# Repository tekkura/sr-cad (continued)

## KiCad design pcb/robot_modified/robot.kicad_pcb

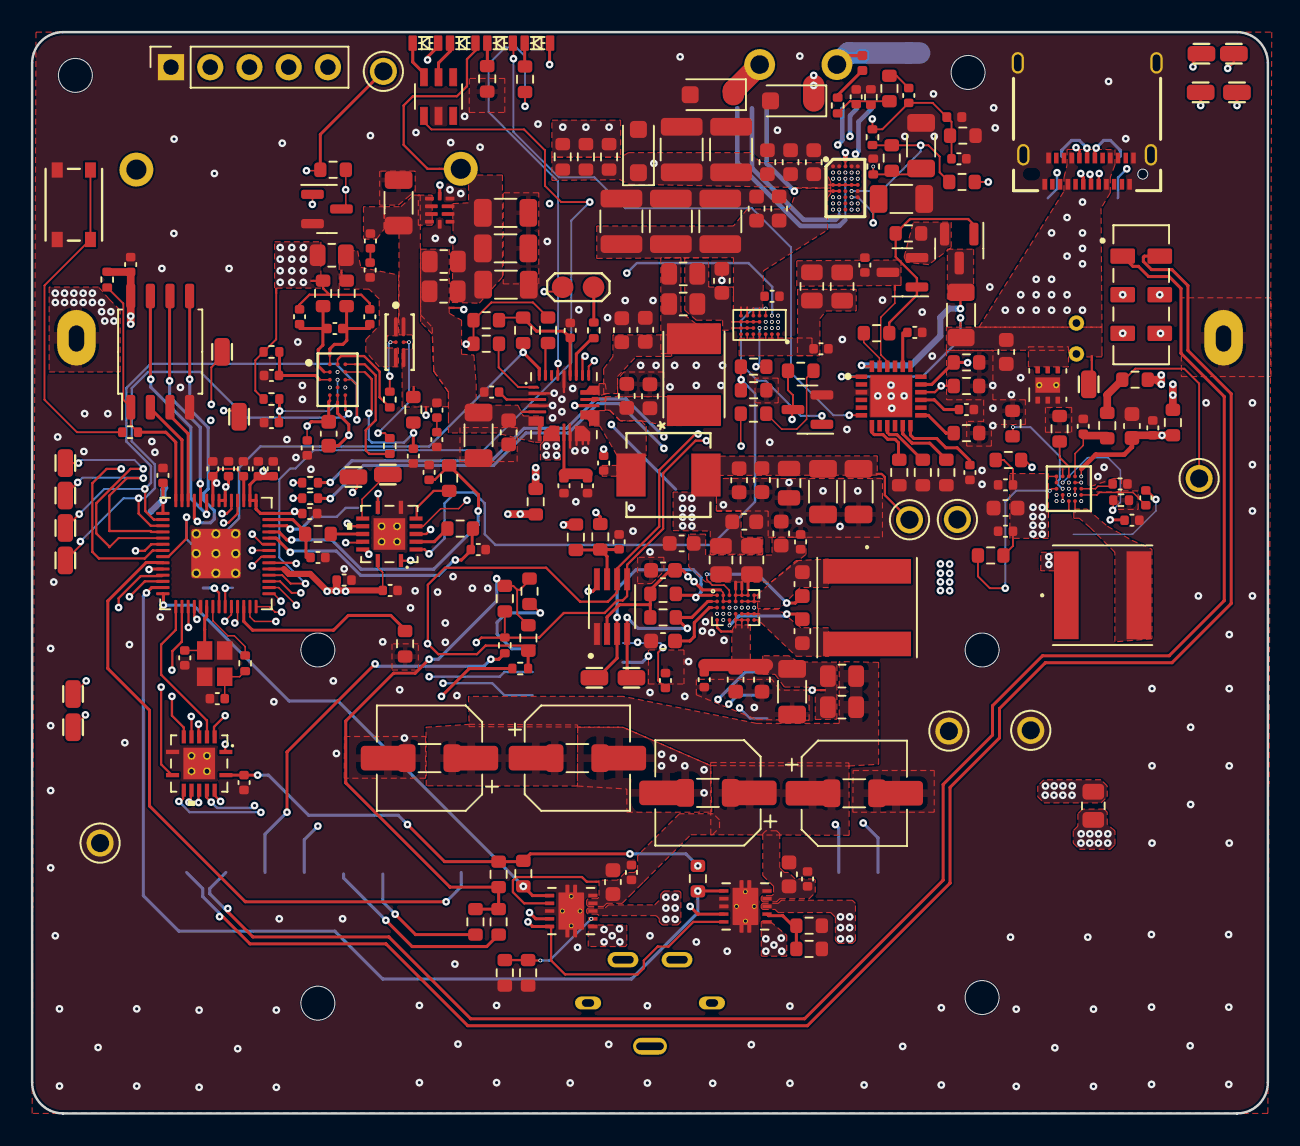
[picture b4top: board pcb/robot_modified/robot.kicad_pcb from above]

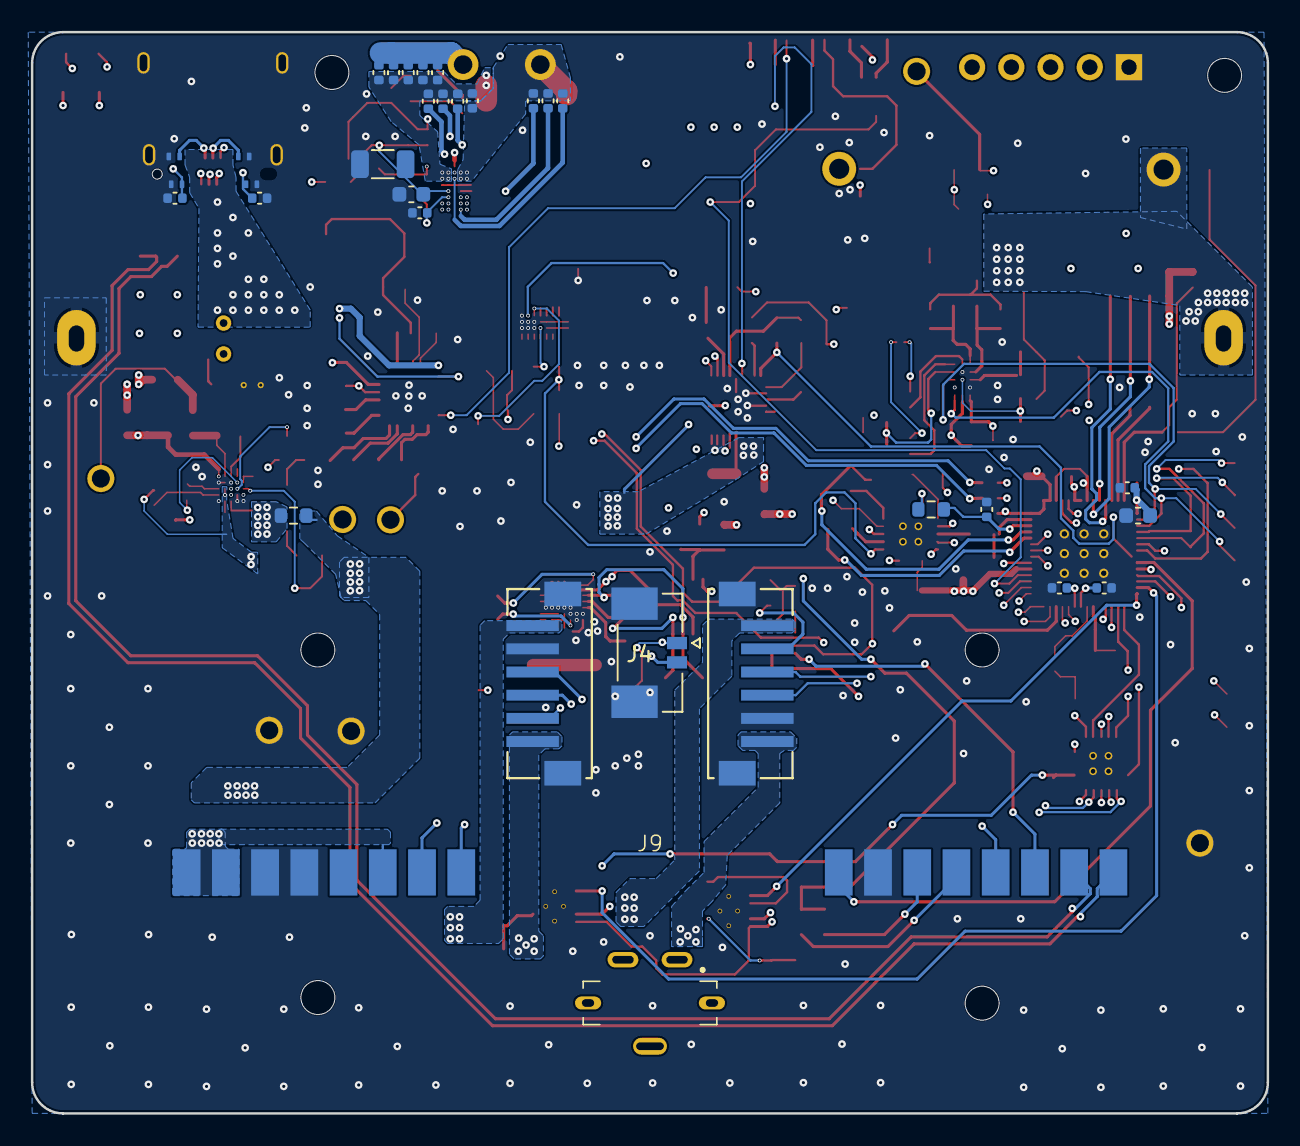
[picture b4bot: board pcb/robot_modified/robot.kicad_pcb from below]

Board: 4 copper layers, 80.0 x 70.0 mm, 318 parts (39 on the bottom side), 202 nets.

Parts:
BT1: DNP; battery26650_holderOnly
BT2: DNP; battery26650
C1, C33, C34, C76, C78, C87, C93: 22uF; C_0603_1608Metric
C2, C3, C18, C19: 27pF; C_0402_1005Metric
C4, C8, C10, C21, C22, C29, C55, C69, C88, C94, C95, C99, C105, C126: 1uF; C_0402_1005Metric
C5, C6, C7, C9, C11, C12, C13, C14, C15, C16, C24, C32, C35, C36, C37, C38, C39, C40, C41, C44, C57, C58, C59, C60, C61, C62, C63, C64, C65, C66, C70, C71, C72, C73, C85, C92, C102, C103, C104, C113, C114, C116, C119, C121: 0.1uF; C_0402_1005Metric
C17, C20, C25, C27, C42, C43, C67, C68, C75, C77, C80, C129, C130, C132, C134, C136: 10uF; C_0603_1608Metric
C23, C124: 4.7uF; C_0603_1608Metric
C26, C56: 0.47uF; C_0603_1608Metric
C28: 2.2uF; C_0603_1608Metric
C30, C31: 0.22uF; C_0603_1608Metric
C74, C86, C89, C90: 100uF; CP_Elec_APXJ100ARA271MF61G
C79, C82, C83, C91, C96, C106, C107, C108, C109, C125, C127: 100uF; C_1206_3216Metric
C81: 47uF; C_0805_2012Metric
C84, C115, C118: 10nF; C_0402_1005Metric
C110, C117, C120: 22nF; C_0402_1005Metric
C111: 1.5nF; C_0402_1005Metric
C112, C122: 3.3nF; C_0402_1005Metric
C123, C128: 47nF; C_0402_1005Metric
C131, C133, C135, C137, C138: 100uF; C_1210_3225Metric
D1: LED-RED; B12H1UYG-20D000134U1930
D2: LED-YG; B12H1UYG-20D000134U1930
D3: LED-Amber; B12H1UYG-20D000134U1930
D4, D6, D10: SMF13A; D_SOD-123F
D5: LED-GREEN; B12H1UYG-20D000134U1930
D7: D_Schottky; SD2114S040S8R0
D9, D11: IN4448HLP; D_0402_1005Metric
H1, H2, H5, H6: MountingHole; MountingHole_2.2mm_M2_2mm_clearance
H3, H4: MountingHole; MountingHole_2.2mm_M2
IC1: TPS22998RYZR
J1: USBC_Receptacle_SMD_RA; CON_USB3.1-C_RCPT_SMD_RA_ACP_12401610E4#2A
J2: Conn_01x05; PinSocket_1x05_P2.54mm_Vertical
J3, J5: Conn_01x06_MountingPin; CONN_B6B-ZR-SM4-TF_JST
J4: USB4151-GF-C; GCT_USB4151-GF-C_REVA
J8: Conn_01x02; THT_Pitch5mm_Drill1.2mm
J9: Conn_01x16; SMD FOR CASTELLATED 1x16 2.54mm
L1, L3: 1.5uH; NRS6028T1R5NMGJ
L2: 0.47uH; Vishay-IHLP-2020BZ-FP_1.905x2.79-3D_2.0-0-0-MFG
NT1, NT2, NT3, NT4, NT5, NT6, NT7, NT8, NT9, NT10, NT11, NT12, NT13, NT14, NT15, NT16, NT17, NT18, NT20: NetTie_2; NetTie-_SMD_Pad6mil
Q1, Q7: Q_NMOS_GDS; SOT-23
Q2: EFC8811R-TF; ON_Semiconductor-568AL-10_2013-O-MFG
Q3: AS2312; SOT-23
Q4: YJL3416A; SOT-23
Q5, Q6: SN74AHC125RGYR
R1, R5, R46, R47, R50: 1k; R_0402_1005Metric
R2: DNP; R_0402_1005Metric
R3, R4: 27; R_0402_1005Metric
R6, R7, R41, R42: 10; R_0402_1005Metric
R8, R18: 47K; R_0603_1608Metric
R9: 80.6k; R_0402_1005Metric
R10, R76, R79, R80, R81, R82, R83, R84, R85, R86, R87, R88, R90, R91, R92, R93, R94: 0; R_0603_1608Metric
R11, R52, R54, R67, R68, R69, R70, R71, R72, R77, R78: 0; R_0805_2012Metric
R14, R15, R20, R21: 2.2k; R_0603_1608Metric
R16: 510k; R_0603_1608Metric
R17, R49, R59, R60, R61, R89, R99: 100k; R_0603_1608Metric
R19: 200k; R_0603_1608Metric
R22, R23, R24, R25, R56, R58, R97: 100; R_0603_1608Metric
R26, R27, R29, R30: 0.39; R_0603_1608Metric
R28, R31, R96, R102: 10k; R_0603_1608Metric
R43, R45, R103, R104, R105: 200; R_0603_1608Metric
R44: 5m; R_0805_2012Metric
R48: 2k; R_0603_1608Metric
R51: 10m; R_1206_3216Metric
R53: 113K; R_0603_1608Metric
R55: 14k; R_0603_1608Metric
R62: 16k; R_0603_1608Metric
R63, R64: 5.1k; R_0603_1608Metric
R66: DNP; R_0603_1608Metric
R98: 150k; R_0402_1005Metric
R100: 220k; R_0402_1005Metric
R101: 6.8k; R_0402_1005Metric
S2: PTS815 SJM 250 SMTR LFS; SW4_PTS815 SJM 250 SMTR LFS_CNK
S3: JS202011JCQN; SW_JS202011JCQN
SW1: SW_SPST; MOLEX_picoblade_SMT_2pin
TH1: DNP; battery26650_thermistor
TH2: 100k; R_0402_1005Metric
TP1, TP2, TP9, TP10, TP11, TP16, TP17, TP18, TP19, TP20, TP21, TP22, TP23, TP24, TP26, TP27, TP33: SMD_0603; TestPoint_SMD_0603
TP12: TP2PinPads; TestPoint_2Pads_Pitch2mm_SMD
TP28, TP29: TestPoint; THT_JumperLead
TP30, TP34, TP39, TP40, TP41, TP42, TP43: TestPoint; KEYSTONE_5002
U1: STWLC38JRM; BGA40C40P5X8_213X333X57
U2: W25Q128JVS; SOIC-8_5.23x5.23mm_P1.27mm
U3: RP2040; RP2040-QFN-56
U4: NCP3901
U5: LSF0102DCTR; SOP65P400X130-8N
U6: MAX77857BEWB+; WLP-35_7x5_2.828x2.028mm
U7: AP2502KTR-G1; SOT95P280X145-6N
U8, U9: DRV8830DRCR; IC_DRV8830DRCR
U12: BQ27742YZFR-G1; Texas_Instruments-YZF0015-0-0-MFG
U13: MAX77976EFD+; MAX77976
U14: MAX77642ANA+; Maxim-N252B2-1-0-A-MFG
U18: AP33771DKZ-13; AP33771DKZ13
U25: TVS0500DRV; TVS0500DRVR
U26, U27, U28, U29: TPD1E05U06; TPD1E05U06DPYR
Y1: ECS-120-8-36-CKM-TR3; XTAL_ECS-120-8-36-CKM-TR3

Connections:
/1V8: R83.2, R91.2, TP40.1
/3V3: R8.1, R14.1, R15.1, R76.2, R79.2, R80.2, R81.2, R82.2, R84.2, R85.2, R86.1, R87.1, R88.2, R94.2, TP39.1
/ADC0: Q5.2 (1A), R16.2, R17.1
/BoostRegulator/1V8: C26.1, R20.1, R21.1, R83.1, U5.2 (VREF_A), U6.A2 (VIO), U6.B2 (EN), U6.B3 (EN)
/BoostRegulator/3V3: C24.1, R19.1, R82.1, U5.7 (VREF_B)
/BoostRegulator/IN: C25.1, C27.1, C29.2, R69.2, R70.2, U6.A4 (IN), U6.A5 (IN), U6.A6 (IN), U6.B4 (IN)
/Charger/BATT: C75.1, C79.1, NT5.1, NT6.1, R77.2, R78.2, U13.6 (BATT), U13.7 (BATT), U13.8 (BATT)
/Charger/BATT_SIGNAL: NT5.2, U13.5 (BATSP)
/Charger/DISQBAT: R80.1, U13.1 (DISQBAT)
/Charger/PVDD: C69.1, C70.1, U13.12 (PVDD)
/Charger/SUSPND: R81.1, U13.31 (SUSPND)
/Charger/VIO: C71.1, R49.1, R79.1, U13.27 (VIO)
/Charger/V_IN: C67.1, C68.1, D7.2 (Anode), R67.2, R68.2, U13.22 (CHGIN), U13.23 (CHGIN)
/DN1: J9.16, S3.4
/DN2: J1.A7 (D-), J1.B7 (D-), S3.6, U28.1 (I/O)
/DP1: J9.15, S3.1
/DP2: J1.A6 (D+), J1.B6 (D+), S3.3, U29.1 (I/O)
/GPIO4: Q1.3 (D), R18.2, U3.6 (GPIO4)
/GPIO5: U3.7 (GPIO5), U4.D2 (VINA_EN/OTG_EN)
/GPIO6: R49.2, U3.8 (GPIO6), U13.32 (IRQB)
/GPIO7: J9.9, U3.9 (GPIO7)
/GPIO8: Q6.1 (1~OE), Q6.4 (2~OE), Q6.10 (3~OE), Q6.13 (4~OE), U3.11 (GPIO8)
/GPIO9: U1.G4 (ENB), U3.12 (GPIO9)
/GPIO10: R28.2, U3.13 (GPIO10), U8.6 (~FAULT)
/GPIO11: R31.2, U3.14 (GPIO11), U9.6 (~FAULT)
/GPIO12: Q6.3 (1Y), U3.15 (GPIO12)
/GPIO13: Q6.6 (2Y), U3.16 (GPIO13)
/GPIO14: Q6.8 (3Y), U3.17 (GPIO14)
/GPIO15: Q6.11 (4Y), U3.18 (GPIO15)
/GPIO20: Q7.3 (D), R8.2, U3.31 (GPIO20)
/GPIO23: R89.2, U1.H4 (INTB), U3.35 (GPIO23)
/I2C0_SCL: R7.2, R15.2, TP16.1, U1.H5 (SCL), U3.3 (GPIO1), U5.6 (B1), U8.10 (SCL), U9.10 (SCL), U12.E3 (SCL)
/I2C0_SDA: R6.2, R14.2, TP1.1, U1.G5 (SDA), U3.2 (GPIO0), U5.5 (B2), U8.9 (SDA), U9.9 (SDA), U12.C3 (SDA)
/I2C1_SCL: J9.7, TP2.1, U3.5 (GPIO3), U13.24 (SCL)
/I2C1_SDA: J9.8, TP17.1, U3.4 (GPIO2), U13.25 (SDA)
/LDOs/LED_3V3: D2.1 (K), U7.6 (LED1)
/LDOs/SYS: C4.1, C85.1, C87.1, R90.2, R92.2, R93.2, U14.A1 (SYSA), U14.B1 (SYSA), U14.E3 (IN_SBB)
/LED_EN: U3.32 (GPIO21), U7.1 (EN)
/LED_PACK: D3.1 (K), U7.5 (LED2)
/MCU/3V3: C5.1, C9.1, C10.1, C11.1, C12.1, C13.1, C14.1, C15.1, C16.1, C17.1, C35.1, Q5.14 (VCC), R2.1, R86.2, U2.8 (VCC), U3.1 (IOVDD), U3.10 (IOVDD), U3.22 (IOVDD), U3.33 (IOVDD), U3.42 (IOVDD), U3.43 (ADC_AVDD), U3.44 (VREG_IN), U3.48 (USB_VDD), U3.49 (IOVDD)
/MCU/ADC2: Q5.9 (3A), TP26.1
/MCU/ADC3: Q5.12 (4A), TP27.1
/MCU/D+: R3.1, S3.2, TP20.1
/MCU/D-: R4.1, S3.5, TP21.1
/MCU/GPIO22: Q5.1 (1~OE), Q5.4 (2~OE), Q5.10 (3~OE), Q5.13 (4~OE), U3.34 (GPIO22)
/MCU/GPIO24: TP10.1, U3.36 (GPIO24)
/MCU/GPIO25: TP33.1, U3.37 (GPIO25)
/MCU/GPIO26_ADC0: C39.1, R25.1, U3.38 (GPIO26_ADC0)
/MCU/GPIO27_ADC1: C38.1, R24.1, U3.39 (GPIO27_ADC1)
/MCU/GPIO28_ADC2: C37.1, R23.1, U3.40 (GPIO28_ADC2)
/MCU/GPIO29_ADC3: C36.1, R22.1, U3.41 (GPIO29_ADC3)
/MCU/QSPI_SCLK: U2.6 (CLK), U3.52 (QSPI_SCLK)
/MCU/QSPI_SD0: U2.5 (DI(IO0)), U3.53 (QSPI_SD0)
/MCU/QSPI_SD1: U2.2 (DO(IO1)), U3.55 (QSPI_SD1)
/MCU/QSPI_SD2: U2.3 (IO2), U3.54 (QSPI_SD2)
/MCU/QSPI_SD3: U2.7 (IO3), U3.51 (QSPI_SD3)
/MCU/QSPI_SS: R1.1, R2.2, U2.1 (~CS), U3.56 (QSPI_SS)
/MCU/RUN: R10.2, U3.26 (RUN)
/MCU/SWCLK: J2.2, U3.24 (SWCLK)
/MCU/SWD: J2.3, U3.25 (SWD)
/MCU/UART_CTS: TP11.1, U3.29 (GPIO18)
/MCU/UART_RTS: TP24.1, U3.30 (GPIO19)
/MCU/UART_RX: J2.5, U3.28 (GPIO17)
/MCU/UART_TX: J2.4, U3.27 (GPIO16)
/MCU/XIN: C2.1, U3.20 (XIN), Y1.1
/MCU/XOUT: R5.1, U3.21 (XOUT)
/MCU/~USB_BOOT: R1.2, S2.1, S2.2
/MOTORS/ENC_11: J5.3, Q6.2 (1A)
/MOTORS/ENC_12: J5.4, Q6.5 (2A)
/MOTORS/ENC_21: J3.4, Q6.9 (3A)
/MOTORS/ENC_22: J3.3, Q6.12 (4A)
/MOTORS/ENC_VCC: J3.5, J5.5, R84.1
/MOTORS/OUT_N1: J5.6, U8.1 (OUT2)
/MOTORS/OUT_N2: J3.1, U9.1 (OUT2)
/MOTORS/OUT_P1: J5.1, U8.3 (OUT1)
/MOTORS/OUT_P2: J3.6, U9.3 (OUT1)
/MOTORS/VCC: C40.1, C41.1, C42.1, C43.1, C74.1, C86.1, C89.1, C90.1, NT17.2, R71.1, R72.1, U8.4 (VCC), U9.4 (VCC)
/MOTORS/VIO: C44.1, Q6.14 (VCC), R28.1, R31.1, R85.1
/PowerMux/FLAG: Q1.1 (G), U4.D3 (VINB_EN/FLAG)
/PowerMux/VIN_A: C21.1, R52.2, R54.2, U4.A1 (VINA), U4.A2 (VINA), U4.A3 (VINA), U4.A4 (VINA), U4.A5 (VINA), U4.A6 (VINA), U4.A7 (VINA)
/PowerMux/VIN_B: C22.1, C129.2, C130.2, C131.2, C133.2, C135.2, U1.E1 (VOUT_1), U1.E2 (VOUT_2), U4.D4 (VINB), U4.D5 (VINB), U4.D6 (VINB), U4.D7 (VINB)
/PowerMux/VIO: R18.1, R76.1
/PowerMux/VOUT: C23.1, R67.1, R68.1, U4.B5 (OUT), U4.B6 (OUT), U4.B7 (OUT), U4.C4 (OUT), U4.C5 (OUT), U4.C6 (OUT), U4.C7 (OUT)
/Protection/PACK+: C106.1, C107.1, C108.1, IC1.6 (VOUT_1), IC1.7 (VOUT_2), IC1.8 (VOUT_3), NT7.1, R77.1, R78.1, TP29.1
/Protection/RC2: Q7.1 (G), U12.D3 (RC2)
/SCL_SL: J9.13, R7.1
/SDA_SL: J9.14, R6.1
/SYS: C1.1, C76.1, C78.1, C81.1, C82.1, C83.1, L2.2, NT11.1, NT14.2, NT20.1, R11.2, R69.1, R70.1, U13.9 (SYS), U13.10 (SYS), U13.11 (SYS)
/USB-PD-ExtChg/CC1: C18.1, J1.A5 (CC1), R63.1, TP22.1, U18.17 (CC1), U26.1 (I/O)
/USB-PD-ExtChg/CC2: C19.1, J1.B5 (CC2), R64.1, TP23.1, U18.16 (CC2), U27.1 (I/O)
/USB-PD-ExtChg/VBUS_EXT: C20.1, J1.A4 (VBUS), J1.A9 (VBUS), J1.B4 (VBUS), J1.B9 (VBUS), NT1.2, NT2.1, R51.1, U25.4 (IN), U25.5 (IN), U25.6 (IN)
/USB-PD-ExtChg/VOUT: C105.1, NT4.1, Q4.3 (D), R52.1, R54.1
/USB-PD-PhonePC/USB_Phone_SYS: J9.1, J9.2, NT18.2, R11.1
/USB-PD-PhonePC/VCIN: J9.6, NT18.1
/USB-PD-PhonePC/VIO1: J9.12, R87.2
/USB-PD-PhonePC/VIO2: J9.11, R88.1
/VBoost: C32.2, C33.2, C34.2, C91.1, NT15.1, NT16.2, R71.2, R72.2, U6.D4 (OUT), U6.E4 (OUT), U6.E5 (OUT), U6.E6 (OUT)
/VRect: C132.2, C134.2, C136.2, C137.2, C138.2, D10.1 (K), Q5.5 (2A), R103.2, R104.2, R105.2, U1.D1 (VRECT_1), U1.D2 (VRECT_2), U1.D3 (VRECT_3), U1.D4 (VRECT_4), U1.D5 (VRECT_5)
/Wireless-Receiver/IEXT: R103.1, R104.1, R105.1, U1.A3 (IEXT)
/Wireless-Receiver/VAA: C124.2, C125.2, R89.1, R98.2, R102.1, U1.E4 (VAA)
/Wireless-Receiver/VDD: C126.2, C127.2, U1.F4 (VDD)
GND: BT1.2 (-), C1.2, C2.2, C3.2, C4.2, C5.2, C6.2, C7.2, C8.2, C9.2, C10.2, C11.2, C12.2, C13.2, C14.2, C15.2, C16.2, C17.2, C18.2, C19.2, C20.2, C21.2, C22.2, C23.2, C24.2, C25.2, C26.2, C27.2, C28.2, C29.1, C32.1, C33.1, C34.1, C35.2, C36.2, C37.2, C38.2, C39.2, C40.2, C41.2, C42.2, C43.2, C44.2, C55.2, C57.2, C58.2, C64.2, C66.2, C67.2, C68.2, C69.2, C70.2, C71.2, C72.2, C74.2, C75.2, C76.2, C77.2, C78.2, C79.2, C80.2, C81.2, C82.2, C83.2, C85.2, C86.2, C87.2, C88.2, C89.2, C90.2, C91.2, C92.2, C93.2, C94.2, C95.2, C96.2, C99.2, C102.2, C103.2, C104.2, C105.2, C106.2, C107.2, C108.2, C109.2, C111.1, C112.1, C124.1, C125.1, C126.1, C127.1, C129.1, C130.1, C131.1, C132.1, C133.1, C134.1, C135.1, C136.1, C137.1, C138.1, D4.2 (A), D6.2 (A), D10.2 (A), D11.2 (A), IC1.5 (GND), IC1.9 (CT), J1.25 (SHLD), J1.A1 (GND), J1.A12 (GND), J1.B1 (GND), J1.B12 (GND), J2.1, J3.2, J3.MP (MountPin), J5.2, J5.MP (MountPin), J9.3, J9.4, J9.10, Q1.2 (S), Q5.7 (GND), Q5.PAD (GND), Q6.7 (GND), Q6.PAD (GND), Q7.2 (S), R9.2, R10.1, R17.2, R26.2, R27.2, R29.2, R30.2, R53.2, R55.2, R59.1, R60.1, R61.1, R62.2, R63.2, R64.2, R97.2, R99.1, R100.2, S2.3, S2.4, SW1.S1, SW1.S2, TH2.2, TP41.1, TP42.1, TP43.1, U1.A1 (VSSP_1), U1.A2 (VSSP_2), U1.A4 (VSSP_3), U1.A5 (VSSP_4), U1.E5 (VSSA), U1.F5 (VSSD), U2.4 (GND), U3.19 (TESTEN), U3.57 (GND), U4.B1 (GND), U4.B2 (GND), U4.B3 (GND), U4.C1 (MODE), U4.C2 (GND), U4.C3 (GND), U4.D1 (CRTL), U5.1 (GND), U6.C3 (PGND), U6.C4 (PGND), U6.C5 (PGND), U6.C6 (PGND), U6.C7 (PGND), U6.D1 (SEL), U6.D2 (PGND), U6.D3 (PGND), U6.E2 (AGND), U7.2 (GND), U8.5 (GND), U8.7 (A0), U8.8 (A1), U8.11 (GND), U9.5 (GND), U9.8 (A1), U9.11 (GND), U12.B2 (NC), U12.D1 (VSS), U13.2 (THM), U13.4 (BATSN), U13.13 (DGND), U13.14 (PGND), U13.15 (PGND), U13.16 (PGND), U13.28 (AGND), U14.A2 (RSET_SBB2), U14.B3 (RSET_SBB0), U14.B4 (GND), U14.B5 (GND), U14.D2 (EN0), U14.E1 (EN2), U14.E2 (GND), U14.E5 (PGND), U18.3 (GND), U18.25 (EP), U25.1 (GND), U25.2 (GND), U25.3 (GND), U25.7 (GND), U26.2 (GND), U27.2 (GND), U28.2 (GND), U29.2 (GND), Y1.2 (GND), Y1.4 (GND)
unnamed: BT1.1 (+), NT10.1, NT13.2, R44.2, TP28.1
unnamed: C3.1, R5.2, Y1.3
unnamed: C30.2, L1.1, U6.A7 (LX1), U6.B5 (LX1), U6.B6 (LX1), U6.B7 (LX1)
unnamed: C31.1, L1.2, U6.D5 (LX2), U6.D6 (LX2), U6.D7 (LX2), U6.E7 (LX2)
unnamed: C59.2, C61.1, NT10.2, R43.2
unnamed: C62.1, NT12.1, Q2.1 (SOURCE1), Q2.3 (SOURCE1), R44.1
unnamed: C62.2, C63.1
unnamed: C65.2, C66.1
unnamed: C73.2, L2.1, U13.17 (LX), U13.18 (LX), U13.19 (LX)
unnamed: C84.1, L3.1, U14.C4 (LXB), U14.D4 (LXB)
unnamed: C110.2, R96.2
unnamed: C112.2, R96.1, R100.1, R101.2
unnamed: D1.2 (A), NT11.2
unnamed: D1.1 (K), R56.1
unnamed: C92.1, C93.1, D2.2 (A), R94.1, U14.A5 (IN_LDO), U14.C3 (SBB1)
unnamed: D3.2 (A), NT7.2
unnamed: C113.2, C114.2, C115.2, C116.2, C117.2, C119.2, C121.2, C122.1, C128.2, D4.1 (K), U1.B4 (AC1_1), U1.B5 (AC1_2), U1.C4 (AC1_3), U1.C5 (AC1_4)
unnamed: D5.2 (A), U18.6 (GPIO4)
unnamed: D5.1 (K), R97.1
unnamed: C118.2, C120.2, C122.2, C123.2, D6.1 (K), J8.1, U1.B1 (AC2_1), U1.B2 (AC2_2), U1.C1 (AC2_3), U1.C2 (AC2_4)
unnamed: C77.1, C80.1, D7.1 (Cathode), U13.21 (BYP)
unnamed: C113.1, C114.1, C116.1, C119.1, C121.1, D9.2 (A), J8.2
unnamed: D9.1 (K), R101.1
unnamed: C110.1, C111.2, D11.1 (K), R98.1, R99.2, U1.F2 (VS)
unnamed: C99.1, IC1.10 (ON), SW1.1 (A)
unnamed: C63.2, C65.1, C96.1, IC1.1 (VBIAS), IC1.2 (VIN_1), IC1.3 (VIN_2), IC1.4 (VIN_3), NT8.1, NT9.1, Q2.4 (SOURCE2), Q2.6 (SOURCE2)
unnamed: NT1.1, TP9.1
unnamed: NT6.2, TP12.2
unnamed: NT9.2, R48.1
unnamed: NT12.2, R45.2
unnamed: NT13.1, R41.1, R42.1
unnamed: NT14.1, TP30.1
unnamed: NT16.1, TP34.1
unnamed: NT20.2, R90.1
unnamed: Q2.2 (GATE1), R46.1
unnamed: Q2.5 (GATE2), R47.1
unnamed: NT3.1, Q3.3 (D), R51.2
unnamed: Q3.1 (G), Q4.1 (G), R58.1, R66.2
unnamed: Q3.2 (S), Q4.2 (S), R66.1
unnamed: Q5.3 (1Y), R25.2
unnamed: Q5.6 (2Y), R24.2
unnamed: Q5.8 (3Y), R23.2
unnamed: Q5.11 (4Y), R22.2
unnamed: R50.2, TP12.1
unnamed: NT8.2, SW1.2 (B)
unnamed: C128.1, U1.B3 (BOOT1)
unnamed: C123.1, U1.C3 (BOOT2)
unnamed: C115.1, U1.G1 (COMA1)
unnamed: C118.1, U1.G2 (COMA2)
unnamed: C117.1, U1.H1 (COMB1)
unnamed: C120.1, U1.H2 (COMB2)
unnamed: C109.1, R102.2, TH2.1, U1.F1 (NTC)
unnamed: R4.2, U3.46 (USB_DM)
unnamed: R3.2, U3.47 (USB_DP)
unnamed: C6.1, C7.1, C8.1, U3.23 (DVDD), U3.45 (VREG_VOUT), U3.50 (DVDD)
unnamed: R16.1, U4.B4 (VINA_S)
unnamed: R21.2, TP18.1, U5.3 (A1), U6.A1 (SCL)
unnamed: R20.2, TP19.1, U5.4 (A2), U6.B1 (SDA)
unnamed: R19.2, U5.8 (EN)
unnamed: C30.1, U6.A3 (BST1)
unnamed: C31.2, U6.E3 (BST2)
unnamed: NT15.2, U6.E1 (FB)
unnamed: C28.1, U6.C1 (VL)
unnamed: R26.1, R29.1, U8.2 (ISENSE)
unnamed: NT17.1, U9.7 (A0)
unnamed: R27.1, R30.1, U9.2 (ISENSE)
unnamed: C57.1, R42.2, U12.C2 (BAT)
unnamed: R46.2, U12.A2 (CHG)
unnamed: R47.2, U12.A3 (DSG)
unnamed: C64.1, R48.2, U12.B3 (PACKP)
unnamed: C55.1, C56.1, TH1.1, U12.E1 (REG25)
unnamed: C59.1, C60.1, R43.1, U12.B1 (SRN)
unnamed: C60.2, C61.2, R45.1, U12.A1 (SRP)
unnamed: C56.2, TH1.2, U12.E2 (TS)
unnamed: C58.1, R41.2, U12.C1 (VPWR)
unnamed: C73.1, U13.20 (BST)
unnamed: R50.1, U13.26 (EXTSM)
unnamed: R56.2, U13.29 (STAT)
unnamed: C72.1, U13.3 (VDD)
unnamed: C84.2, U14.D5 (BST)
unnamed: R92.1, U14.D1 (EN1)
unnamed: R93.1, U14.C1 (ENLDO)
unnamed: C88.1, R91.1, U14.A4 (LDO)
unnamed: L3.2, U14.E4 (LXA)
unnamed: R55.1, U14.C2 (RSET_IPK)
unnamed: R9.1, U14.B2 (RSET_LDO)
unnamed: R53.1, U14.A3 (RSET_SBB1)
unnamed: C94.1, U14.C5 (SBB0)
unnamed: C95.1, U14.D3 (SBB2)
unnamed: C104.1, U18.15 (IFB)
unnamed: NT2.2, U18.1 (ISENP)
unnamed: R62.1, U18.13 (PSEL)
unnamed: R58.2, U18.23 (PWR_EN)
unnamed: C102.1, U18.12 (V3VD)
unnamed: C103.1, U18.20 (V5V)
unnamed: NT4.2, U18.22 (VBUS)
unnamed: NT3.2, U18.24 (VCC)
unnamed: R60.2, U18.9 (VSEL0)
unnamed: R59.2, U18.7 (VSEL1)
unnamed: R61.2, U18.11 (VSEL2)

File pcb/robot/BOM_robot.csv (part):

"Reference";"Qty";"Part Number";"Value";"DNP";"Exclude from BOM";"Exclude from Board";"Footprint";"Manufacturer"
"BT1";"1";"a15042300ux0145";"DNP";"DNP";"";"";"robot:battery26650_holderOnly";"Uxcell"
"BT2";"1";"26650-5000-1";"DNP";"DNP";"";"";"robot:battery26650";"Suprise Collection"
"C1,C33,C34,C76,C78,C87,C93";"7";"GRM188R61A226ME15D";"22uF";"";"";"";"robot:C_0603_1608Metric";"Murata"
"C2,C3,C18,C19";"4";"GRM1555C1H270JA01J";"27pF";"";"";"";"robot:C_0402_1005Metric";"Murata"
"C4,C8,C10,C21,C22,C29,C55,C69,C88,C94,C95,C105,C126";"13";"GRM155R61E105KA12D";"1uF";"";"";"";"robot:C_0402_1005Metric";"Murata"
"C5,C6,C7,C9,C11,C12,C13,C14,C15,C16,C24,C32,C35,C36,C37,C38,C39,C40,C41,C44,C57,C58,C59,C60,C61,C62,C63,C64,C65,C66,C70,C71,C72,C73,C85,C92,C102,C103,C104";"39";"CL05A104KA5NNNC";"0.1uF";"";"";"";"robot:C_0402_1005Metric";"Samsung"
"C17,C20,C25,C27,C42,C43,C67,C68,C75,C77,C80,C129,C130,C132,C134,C136";"16";"GRM188R61E106KA73J";"10uF";"";"";"";"robot:C_0603_1608Metric";"Murata"
"C23,C124";"2";"GRM188R61E475KE11D";"4.7uF";"";"";"";"robot:C_0603_1608Metric";"Murata"
"C26,C56";"2";"CL10B474KO8NNNC";"0.47uF";"";"";"";"robot:C_0603_1608Metric";"Samsung"
"C28";"1";"CL10A225KP8NNNC";"2.2uF";"";"";"";"robot:C_0603_1608Metric";"Samsung"
"C30,C31";"2";"CL10B224KA8NNNC";"0.22uF";"";"";"";"robot:C_0603_1608Metric";"Samsung"
"C74,C86,C89,C90";"4";"GRM31CD80J107MEA8K";"100uF";"DNP";"";"";"robot:CP_Elec_APXJ100ARA271MF61G";"Murata"
"C79,C91,C96,C106,C107,C108";"6";"GRM31CD80J107MEA8K";"100uF";"DNP";"";"";"robot:C_1206_3216Metric";"Murata"
"C81";"1";"CL21A476MRYNNNE";"47uF";"";"";"";"robot:C_0805_2012Metric";"Samsung Electro-Mechanics"
"C82,C83,C109,C125,C127";"5";"GRM31CD80J107MEA8K";"100uF";"";"";"";"robot:C_1206_3216Metric";"Murata"
"C84,C115,C118";"3";"885012205067";"10nF";"";"";"";"robot:C_0402_1005Metric";"Würth Elektronik"
"C99";"1";"GRM155R61E105KA12D";"1uF";"DNP";"";"";"robot:C_0402_1005Metric";"Murata"
"C110,C117,C120";"3";"GRM155R71H223KA12J";"22nF";"";"";"";"robot:C_0402_1005Metric";"Murata"
"C111";"1";"GCM155R71H152KA37D";"1.5nF";"";"";"";"robot:C_0402_1005Metric";"Murata"
"C112,C122";"2";"GCM155R71H332KA37J";"3.3nF";"";"";"";"robot:C_0402_1005Metric";"Murata"
"C113,C114,C116,C119,C121";"5";"GRM155R62A104KE14D";"0.1uF";"";"";"";"robot:C_0402_1005Metric";"Murata"
"C123,C128";"2";"GRM155R71H473KE14D";"47nF";"";"";"";"robot:C_0402_1005Metric";"Murata"
"C131";"1";"GRM31CD80J107MEA8K";"100uF";"";"";"";"robot:C_1210_3225Metric";"Murata"
"C133,C135,C138";"3";"GMC32X5R107M16NT";"100uF";"DNP";"";"";"robot:C_1210_3225Metric";"Cal-Chip Electronics, Inc."
"C137";"1";"GMC32X5R107M16NT";"100uF";"";"";"";"robot:C_1210_3225Metric";"Cal-Chip Electronics, Inc."
"D1";"1";"B12H1USD-20D000234U1930";"LED-RED";"";"";"";"robot:B12H1UYG-20D000134U1930";"Harvatek Corporation"
"D2";"1";"B12H1UYG-20D000134U1930";"LED-YG";"";"";"";"robot:B12H1UYG-20D000134U1930";"Harvatek Corporation"
"D3";"1";"B12H1UY--20D000134U1930";"LED-Amber";"";"";"";"robot:B12H1UYG-20D000134U1930";"Harvatek Corporation"
"D4,D6,D10";"3";"SMF13A";"SMF13A";"";"";"";"robot:D_SOD-123F";"Littelfuse Inc."
"D5";"1";"B12H1NG--20D000134U1930";"LED-GREEN";"";"";"";"robot:B12H1UYG-20D000134U1930";"Harvatek Corporation"
"D7";"1";"SD2114S040S8R0";"D_Schottky";"";"";"";"robot:SD2114S040S8R0";"KYOCERA AVX"
"D9,D11";"2";"1N4448HLP-7";"IN4448HLP";"";"";"";"robot:D_0402_1005Metric";"Diodes Incorporated"
"H1,H2,H5,H6";"4";"N/A";"MountingHole";"";"Excluded from BOM";"";"robot:MountingHole_2.2mm_M2_2mm_clearance";"N/A"
"H3,H4";"2";"N/A";"MountingHole";"";"Excluded from BOM";"";"robot:MountingHole_2.2mm_M2";"N/A"
"IC1";"1";"TPS22998RYZR";"TPS22998RYZR";"";"";"";"robot:TPS22998RYZR";"Texas Instruments"
"J1";"1";"12401610E4#2A";"USBC_Receptacle_SMD_RA";"";"";"";"robot:CON_USB3.1-C_RCPT_SMD_RA_ACP_12401610E4#2A";"Amphenol Commercial Products"
"J2";"1";"PH1-05-UA";"Conn_01x05";"";"";"";"robot:PinSocket_1x05_P2.54mm_Vertical";"Adam Tech"
"J3,J5";"2";"B6B-ZR-SM4-TF";"Conn_01x06_MountingPin";"";"";"";"robot:CONN_B6B-ZR-SM4-TF_JST";"JST"
"J6,J7";"2";"A06ZR06ZR28H51B";"MotorCable";"DNP";"";"Excluded from board";"";"JST"
"J8";"1";"N/A";"Conn_01x02";"";"Excluded from BOM";"";"robot:THT_Pitch5mm_Drill1.2mm";"N/A"
"J9";"1";"";"Conn_01x16";"";"";"";"robot:SMD FOR CASTELLATED 1x16 2.54mm";""
"L1,L3";"2";"NRS6028T1R5NMGJ";"1.5uH";"";"";"";"robot:NRS6028T1R5NMGJ";"TAIYO YUDEN"
"L2";"1";"IHLP2020BZERR47M01";"0.47uH";"";"";"";"robot:Vishay-IHLP-2020BZ-FP_1.905x2.79-3D_2.0-0-0-MFG";"Vishay"
"L5";"1";"760308102207";"8uH";"DNP";"";"Excluded from board";"";"Würth Elektronik"
"M1,M2";"2";"4639";"~";"DNP";"";"Excluded from board";"";"Adafruit"
"NT1,NT2,NT3,NT4,NT5,NT6,NT7,NT8,NT9,NT10,NT11,NT12,NT13,NT14,NT15,NT16,NT17,NT18,NT20";"19";"N/A";"NetTie_2";"";"Excluded from BOM";"";"robot:NetTie-_SMD_Pad6mil";"N/A"
"Q1,Q7";"2";"BSS138";"Q_NMOS_GDS";"";"";"";"robot:SOT-23";"ANBON SEMICONDUCTOR (INT'L) LIMITED"
"Q2";"1";"EFC8811R-TF";"EFC8811R-TF";"";"";"";"robot:ON_Semiconductor-568AL-10_2013-O-MFG";"ON Semiconductor"
"Q3";"1";"AS2312";"AS2312";"";"";"";"robot:SOT-23";"ANBON SEMICONDUCTOR (INT'L) LIMITED"
"Q4";"1";"YJL3416A";"YJL3416A";"";"";"";"robot:SOT-23";"Yangjie Electronic Technology "
"Q5,Q6";"2";"SN74AHC125RGYR";"SN74AHC125RGYR";"";"";"";"robot:SN74AHC125RGYR";"Texas Instruments"
"R1,R5,R46,R47,R50";"5";"WR04X102 JTL";"1k";"";"";"";"robot:R_0402_1005Metric";"Walsin Technologies"
"R2";"1";"DNP";"DNP";"DNP";"Excluded from BOM";"";"robot:R_0402_1005Metric";"DNP"
"R3,R4";"2";"RMCF0402JT27R0";"27";"";"";"";"robot:R_0402_1005Metric";"Stackpole Electronics"
"R6,R7,R41,R42";"4";"RC0402FR-1310RL";"10";"";"";"";"robot:R_0402_1005Metric";"Yageo"
"R8,R18";"2";"RMCF0603JT47K0";"47K";"";"";"";"robot:R_0603_1608Metric";"Stackpole Electronics"
"R9";"1";"RMCF0402FT80K6";"80.6k";"";"";"";"robot:R_0402_1005Metric";"Stackpole Electronics"
"R10,R80,R81";"3";"RMCF0603ZT0R00";"0";"DNP";"";"";"robot:R_0603_1608Metric";"Stackpole Electronics"
"R11,R52,R54,R67,R68,R69,R70,R71,R72,R77,R78";"11";"RMCF0805ZT0R00";"0";"";"";"";"robot:R_0805_2012Metric";"Stackpole Electronics"
"R14,R15,R20,R21";"4";"RMCF0603JT2K20";"2.2k";"";"";"";"robot:R_0603_1608Metric";"Stackpole Electronics"
"R16";"1";"RMCF0603JT510K";"510k";"";"";"";"robot:R_0603_1608Metric";"Stackpole Electronics"
"R17,R49,R59,R60,R61,R89,R99";"7";"WR06X1003FTL";"100k";"";"";"";"robot:R_0603_1608Metric";"Walsin Technology"
"R19";"1";"RMCF0603JT200K";"200k";"";"";"";"robot:R_0603_1608Metric";"Stackpole Electronics"
"R22,R23,R24,R25,R56,R58,R97";"7";"RMCF0603JT100R";"100";"";"";"";"robot:R_0603_1608Metric";"Stackpole Electronics"
"R26,R27";"2";"ERJ-3RQJR39V";"0.39";"DNP";"";"";"robot:R_0603_1608Metric";"Panasonic"
"R28,R31,R96,R102";"4";"WR06X1002FTL";"10k";"";"";"";"robot:R_0603_1608Metric";"Walsin Technology"
"R29,R30";"2";"ERJ-3RQJR39V";"0.39";"";"";"";"robot:R_0603_1608Metric";"Panasonic"
"R43,R45,R103,R104";"4";"ERJ-PA3J201V";"200";"";"";"";"robot:R_0603_1608Metric";"Panasonic"
"R44";"1";"PA0805FRF470R005L";"5m";"";"";"";"robot:R_0805_2012Metric";"Yageo"
"R48";"1";"RMCF0603FT2K00";"2k";"";"";"";"robot:R_0603_1608Metric";"Stackpole Electronics"
"R51";"1";"ERJ-8CWJR010V";"10m";"";"";"";"robot:R_1206_3216Metric";"Panasonic"
"R53";"1";"RMCF0603FT113K";"113K";"";"";"";"robot:R_0603_1608Metric";"Stackpole Electronics"
"R55";"1";"RMCF0603FT14K0";"14k";"";"";"";"robot:R_0603_1608Metric";"Stackpole Electronics"
"R62";"1";"RMCF0603FT16K0";"16k";"";"";"";"robot:R_0603_1608Metric";"Stackpole Electronics"
"R63,R64";"2";"RMCF0603JT5K10";"5.1k";"";"";"";"robot:R_0603_1608Metric";"Stackpole Electronics"
"R66";"1";"DNP";"DNP";"DNP";"Excluded from BOM";"";"robot:R_0603_1608Metric";"DNP"
"R76,R79,R82,R83,R84,R85,R86,R87,R88,R90,R91,R92,R93,R94";"14";"RMCF0603ZT0R00";"0";"";"";"";"robot:R_0603_1608Metric";"Stackpole Electronics"
"R98";"1";"RC0402FR-13150KL";"150k";"";"";"";"robot:R_0402_1005Metric";"YAGEO"
"R100";"1";"RC0402FR-07220KL";"220k";"";"";"";"robot:R_0402_1005Metric";"YAGEO"
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
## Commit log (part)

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2026-01-23 Modularized usb-pd board and main board split
2026-01-23 Update: Finalized design source (Base for fabrication)
2026-01-23 Add_Projects
2026-01-28 Adding USB_PD_Module 3d model for visualization in main board
2026-01-28 Adding usb holes footprint for main board
2026-01-28 Updating main pcb with usb hole and 3d model for module
2026-01-28 Update: Refreshed Gerbers and generated raw BOMs
    I regenerated the motherboard gerbers, saved the modified footprints, and associated them with the schematic.
2026-02-02 BOM generate
2026-02-02 Order and check for BOM availability
2026-02-03 Update BOM list and request
2026-02-03 Full BOM update
2026-02-03 NEXTPCB response
2026-02-03 PCBway Update
2026-02-04 Prices update
2026-03-03 Added the TPS22950CDDCR
    Generation, upgrade, and replacement of devices in BOM for manufacturing at JLCPCB.
2026-03-03 Add Octopart list
    BOM generate
    Order and check for BOM availability
2026-03-19 Price update and final BOM
    The actual prices were added as an image of the order placed, and the BOM downloaded directly from the order was added.
2026-03-19 Data update
    The out-of-stock items and current prices were listed.
2026-03-19 Add prices
2026-03-22 JLCPCB Update and Verification
    The Gerber files were updated, DNP and exclude were removed, Gerber files were uploaded and configured to JLCPCB, Pick and Place and BOM were added, devices were replaced, and factory stock was verif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
2026-03-23 update led
2026-03-23 BOM and stock update Main PCB
    The new Gerber files were added, the old ones were deleted from the motherboard, some devices were replaced, and the price and estimated time were found.
2026-03-23 Gerber update and price quote
2026-03-25 Quotation PCBWay
2026-03-30 Modification and replacement of MAX77642ANA
    The MAX77642ANA was replaced with the LDO XC6206 and the TPS63021DSJR. Rerouting and Gerber updates were performed.
2026-04-01 BOM and pricing update.
2026-04-01 Add comparative price report for USB PD module
2026-04-02 Project and document update
2026-04-06 Price and stock update
2026-04-06 Comparative report of the motherboard and modifications added
